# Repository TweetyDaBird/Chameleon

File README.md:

# The Fat Chameleon 

## Features
**Chameleon is a grid type orthogonal keyboard with two optional layouts in one single PCB.** Being able to break off the bottom row allows both a 5x12 layout similar to the popular Preonic and a 4x12 layout similar to the equally popular little brother Planck on the same PCB. 

Using the more common 19.05 mm grid spacing (vs Preonic & Planck's unique 19 mm) this PCB fit's several popular 'aftermarket' keyboard cases intended for JJ40/JJ50 and BM40 PCB's without modification. (Please read below!)

Being fully hot-swap and with PCB mounted stabilizers, Chameleon adds support for up to four encoders and a bottom row allowing either a single stabilized 2u key or two 2u keys in the middle, allowing for a layout that suits most users. If used as a 5 row keyboard, the bottom encoders can alternatively be placed at the edges on the second row, but **not more than one per corner.** 

The Chameleon features 8 bottomfacing RGB LEDs for underglow effects or to be used for layer indication or similar. 

**Please Note! This PCB does NOT fit a Planck/Preonic case! You will need a different case to complete the build!**

### Main Features:
* QMK and VIAL compatible, fully programmable keyboard**
* RP2040 MCU, Dual-core Arm Cortex M0+ processor, flexible clock running up to 133 MHz
* 264KB of SRAM, and 4MB of on-board Flash memory
* USB-C connector, (USB 1.1 device and host support)
* Low-power sleep and dormant modes
* Drag-and-drop programming using mass storage over USB
* Kaihl hot-swap sockets for Cherry MX compatible switches (3 & 5-pin)
* Cherry Style PCB mounted stabilizers
* Two main layouts:
	* 5x12 with 58 to 60 keys
	* 4x12 with 46 to 48 keys (Break off bottom row) 
* Configurable bottom row:
	* Full 1u grid
	* 1x centered, stabilized 2u key
	* 2x centered,  stabilized 2u keys

### Optional add-ons:
* Support for up to 4 rotary encoders **(one encoder per corner)**
* Optional RGB underglow (8x SK6812 mini-e)
* FR4 Front plate (FR4 material, same as PCB), with full layout options (Black / White). This is designed to fit most/all existing cases of a tray (or burger) mounting type, 3D printed or CNC. Se below for listed tested cases.

**These options requires additional components not included in this listing and sold separately.**

## Assembly
**Little or no tools at all needed!** The PCB can be delivered fully soldered and ready to use, either as a full matrix, or with your selection of rotary encoders (encoders need to be added to the order), or as a "DIY Kit" with the hotswap sockets for the 6 encoder positions not soldered.

The 8 optional RGB LED's needs to be soldered in place if used. (These are pre-soldered together with the encoders/hot-swap sockets at no extra cost, if that option is selected and all parts are purchased in the same order).

# Case & Plate
**The design is made to fit any existing cases for JJ40/JJ50 & BM40 both CNC and 3D printed.** This means that existing cases with an *integrated* plate is then limited to the layout options supported by that case/plate even if the PCB supports more layouts. 

#### Cases verified to work:

- [JJ50 Aluminium & Acrylic Case](https://kprepublic.com/collections/jj50-50/products/anodized-aluminium-case-for-jj50-50-custom-keyboard-acrylic-diffuser-rotary-brace-similar-with-preonic)
- [JJ50 Stainless Steel Case](https://kprepublic.com/collections/jj50-50/products/stainless-steel-bent-case-enclosed-case-for-jj50-jj50-50-custom-keyboard-acrylic-panels-acrylic-panel-diffuser-similar-preonic)
- [JJ40 Aluminium Tray Case](https://kprepublic.com/products/anodized-aluminium-jj40-bm40-flat-case-metal-feet-black-sliver-grey-for-40-mini?_pos=1&_sid=b33f69eef&_ss=r)
- [JJ40 Aluminium & Acrylic Case](https://kprepublic.com/products/anodized-aluminium-case-for-jj40-40-custom-keyboard-acrylic-panels-acrylic-diffuser-jj40-rotary-brace-supporter-for-planck?_pos=4&_sid=b33f69eef&_ss=r)
- [Poseidon PSD40 Case Anodized](https://kprepublic.com/products/poseidon-psd40-case-anodized-aluminium-case-for-custom-mechanical-keyboard-black-siver-grey-blue-red-for-jj40-bm40-bm40-rgb?_pos=5&_sid=b33f69eef&_ss=r) 
- [Poseidon PSD40 Case Electonplated](https://kprepublic.com/products/kp-poseidon-psd40-case-electrophoresis-cnc-case-for-custom-mechanical-keyboard-yellow-purple-cyan-white-for-jj40-bm40-bm40-rgb?_pos=6&_sid=b33f69eef&_ss=r)

*Mounting hardware is associated with the case, and not delivered with the Chameleon PCB and Plate.

## Front Plate
**A front plate in FR4 (PCB core material) is available as an add-on, but may not fit all cases.** To be as much a "one size fit's all" plate, this plate has rounded corners, which may leave gaps in the corners on some cases.

## 3D-print a case
**This is an adaptation of the Olkb Low Pro, ie low profile case for the Planck**, slightly re-designed to fit the 'normal' key spacing of the JJ40/JJ50 PCB and available as two designs to fit either the Planck or Preonic layout. Fully compatible with the FR4 front plate.
- [JJ50 - "Preonic" LoPro case](https://github.com/TweetyDaBird/Chameleon/blob/Development/JJ50_BM50_low_pro.zip)
- [JJ40 & BM40 - "Planck" LoPro case](https://github.com/TweetyDaBird/Chameleon/blob/Development/JJ40_BM40_low_pro.zip)

#### Examples of a 3D-printed case in white (Including the top image):

## Sandwich type case/plates
A full sandwich type case in FR4 material will be added at a later date for those interested, but is for now WIP.

# Making Chameleon yourself
**Chameleon is open source / open hardware, and can be manufactured by anyone. The release contains all the neccesary files like parts lists, positions files etc for a full PCB/SMT production.** 

The formatting and files are geared towards [JLCPCB](http://jlcpcb.com), but never tested as such, as I only manufacture the PCB then do the assembly myself (at least until this reaches a volume justifying full SMT production).

The components are small enough that you would have to be highly skilled to attempt to assemble this either as hand soldered, or small scale/DIY SMT. I would highly recommend ordering the PCB as fully assembled unless you know you have the neccesary skill-set.

## Buy a kit!
I sell complete kits, making it easy to build your keyboard, and it also supports prototypes for new wacky ones. 

## Discord for build help and discussions!

# License

[![CC BY-SA 4.0][cc-by-sa-shield]][cc-by-sa] - This work is licensed under a
[Creative Commons Attribution-ShareAlike 4.0 International License][cc-by-sa].

[cc-by-sa]: http://creativecommons.org/licenses/by-sa/4.0/
[cc-by-sa-shield]: https://img.shields.io/badge/License-CC%20BY--SA%204.0-lightgrey.svg

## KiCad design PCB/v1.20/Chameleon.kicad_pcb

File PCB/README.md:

# Chameleon PCB

## Change Log:
- v1.00 - Initial Release

- v1.01 - Second Release
  - Corrected RGB
  - Tweaked outline for easier removal of bottom row
  
- v1.11 - Third Release
  - Corrected USB Port position
  
- v1.20 - Third Release
  - Corrections to silkscreen.
<<<<<<< HEAD
  - Marking the spacer mounting holes for Planck/Preonic
=======
  - Marking the spacer mounting holes for Planck/Preonic
  - Marking Sockets for layout.
  - Added socket warning.
  - Add CE/RoHS marking.

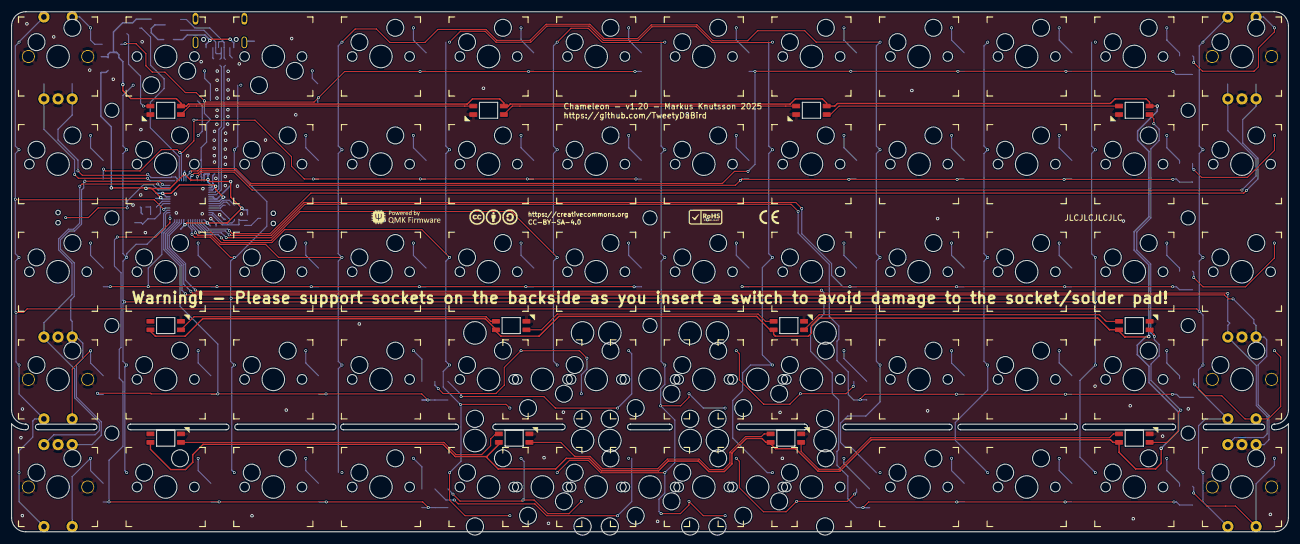
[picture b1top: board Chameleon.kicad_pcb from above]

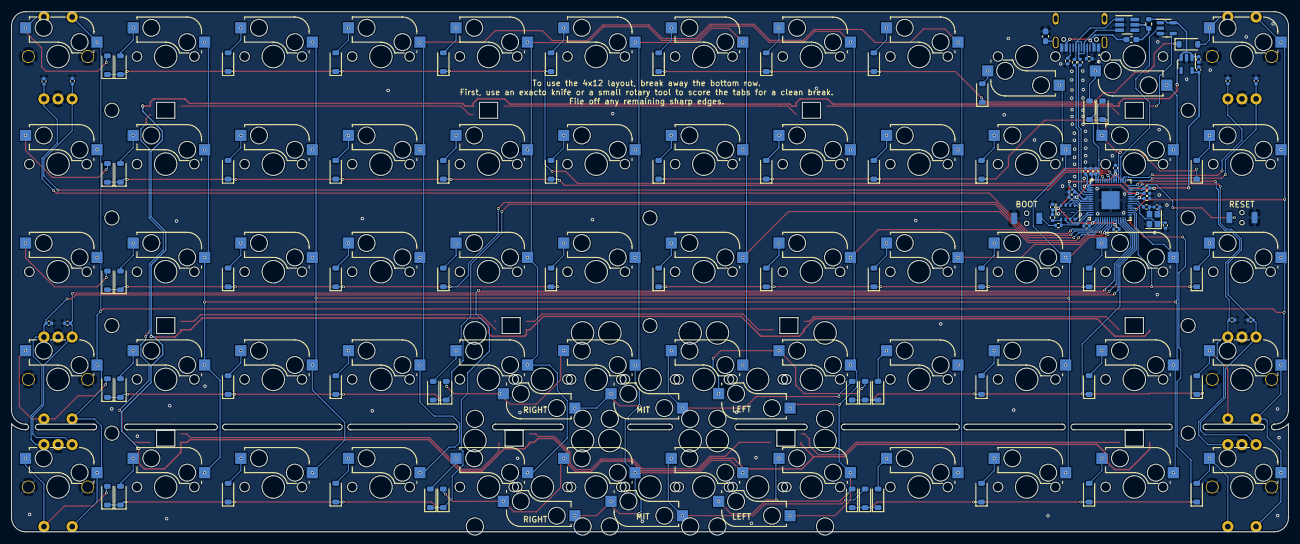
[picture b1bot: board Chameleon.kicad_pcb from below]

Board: 2 copper layers, 226.0 x 92.0 mm, 201 parts (115 on the bottom side), 120 nets.

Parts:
C1, C8, C11, C12: 1uF; C_0402_1005Metric
C2, C3, C4, C5, C6, C7, C9, C10, C13, C16, C17, C18, C19, C20, C21, C22, C23: 100nF; C_0402_1005Metric
C14, C15: 30pF; C_0402_1005Metric
D1, D2, D3, D4, D5, D6, D7, D8, D9, D10, D11, D12, D13, D14, D15, D16, D17, D18, D19, D20, D21, D22, D23, D24, D25, D26, D27, D28, D29, D30, D31, D32, D33, D34, D35, D36, D37, D38, D39, D40, D41, D42, D43, D44, D45, D46, D47, D48, D49, D50, D51, D52, D53, D54, D55, D56, D57, D58, D59, D60: 1N4148W; D_SOD-123
F1: 0603L050/6AR; R_0603_1608Metric
FB1, FB2: BLM18SG700TZ1D; C_0603_1608Metric_Pad1.08x0.95mm_HandSolder
H1, H2, H3, H4, H5, H6, H7, H8, H9, H10: Spacer_PCB; Spacer Plate hole
Logo1: CC-BY-SA-4.0; CC_BY_SA_40_line
Logo2: QMK_Logo; Powered_by_QMK
Logo3: CE
Logo4: RoHS; RoHs
R1, R2: 5.1K; R_0402_1005Metric
R3, R7: 10K; R_0402_1005Metric
R4, R10: 1K; R_0402_1005Metric
R5, R6: 27R; R_0402_1005Metric
RGB1, RGB2, RGB3, RGB4, RGB5, RGB6, RGB7, RGB8, RGB9, RGB10, RGB11, RGB12: SK6812MINI-E; RGB_SK6812MINI-E
ST1, ST2, ST3, ST4, ST5, ST6: Stabilizer_2u_MX; Stabilizer_Cherry_MX_2.00u
SW1, SW12: SW_MX_HotSwap_Encoder
SW2, SW3, SW4, SW5, SW6, SW7, SW8, SW9, SW10, SW11, SW13, SW14, SW15, SW16, SW17, SW18, SW19, SW20, SW21, SW22, SW23, SW24, SW25, SW26, SW27, SW28, SW29, SW30, SW31, SW32, SW33, SW34, SW35, SW36, SW38, SW39, SW40, SW41, SW42, SW43, SW44, SW45, SW46, SW47, SW50, SW51, SW52, SW53, SW54, SW55, SW56, SW57, SW58, SW59, SW61, SW62, SW63, SW64, SW65, SW66: PG151101S11; SW_MX_HotSwap
SW37, SW48, SW49, SW60: SW_MX_HotSwap_Encoder_inverted
TACT1, TACT2: YTSA010
U1: SPX3819M5-L-3-3/TR; SOT-23-5
U2: W25Q32JVUUIQ; USON-8_4x3mm_P0.8mm
U3: RP2040; QFN-56-1EP_7x7mm_P0.4mm_EP3.2x3.2mm
U4: SN74LV1T34DBV; SOT-23-5
U5: SRV05-4; SOT-23-6_Handsoldering
USB1: USB_C_Receptacle_USB2.0; HRO_TYPE-C-31-M-12
Y1: TXM12M0004252LBCEO00T; Crystal_SMD_2520-4Pin_2.5x2.0mm

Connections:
+1V1: C8.1, C9.1, C10.1, U3.23 (DVDD), U3.45 (VREG_VOUT), U3.50 (DVDD)
+3V3: C1.1, C2.1, C3.1, C4.1, C5.1, C6.1, C7.1, C12.1, C13.1, R3.1, R7.1, U1.5 (OUT), U2.8 (VCC), U3.1 (IOVDD), U3.10 (IOVDD), U3.22 (IOVDD), U3.33 (IOVDD), U3.42 (IOVDD), U3.43 (ADC_AVDD), U3.44 (VREG_IN), U3.48 (USB_VDD), U3.49 (IOVDD)
+5V: C11.1, F1.2, RGB1.1 (VDD), RGB2.1 (VDD), RGB3.1 (VDD), RGB4.1 (VDD), RGB5.1 (VDD), RGB6.1 (VDD), RGB7.1 (VDD), RGB8.1 (VDD), RGB9.1 (VDD), RGB10.1 (VDD), RGB11.1 (VDD), RGB12.1 (VDD), U1.1 (IN), U1.3 (EN), U4.5 (VCC)
/DN: R6.1, U3.46 (USB_DM)
/DP: R5.1, U3.47 (USB_DP)
Col_0: SW1.1, SW1.S1, SW12.1, SW12.S1, SW13.1, SW24.1, SW25.1, SW36.1, SW37.1, SW37.S1, SW48.1, SW48.S1, SW49.1, SW49.S1, SW60.1, SW60.S1, U3.18 (GPIO15)
Col_1: SW2.2, SW11.1, SW14.1, SW23.1, SW26.1, SW35.1, SW38.1, SW47.1, SW50.1, SW59.1, U3.17 (GPIO14)
Col_2: SW3.2, SW10.1, SW15.1, SW22.1, SW27.1, SW34.1, SW39.1, SW46.1, SW51.1, SW58.1, U3.8 (GPIO6)
Col_3: SW4.1, SW9.1, SW16.1, SW21.1, SW28.1, SW33.1, SW40.1, SW45.1, SW52.1, SW57.1, U3.7 (GPIO5)
Col_4: SW5.1, SW8.1, SW17.1, SW20.1, SW29.1, SW32.1, SW41.1, SW44.1, SW53.1, SW56.1, SW61.2, SW64.2, U3.6 (GPIO4)
Col_5: SW6.1, SW7.1, SW18.1, SW19.1, SW30.1, SW31.1, SW42.1, SW43.1, SW54.1, SW55.1, SW62.1, SW63.2, SW65.1, SW66.2, U3.5 (GPIO3)
D+: R5.2, U5.1 (IO1), USB1.A6 (D+), USB1.B6 (D+)
D-: R6.2, U5.3 (IO2), USB1.A7 (D-), USB1.B7 (D-)
ENC1_A: C16.1, SW1.A, U3.29 (GPIO18)
ENC1_B: C17.2, SW1.B, U3.30 (GPIO19)
ENC2_A: C18.1, SW12.A, U3.39 (GPIO27_ADC1)
ENC2_B: C19.2, SW12.B, U3.2 (GPIO0)
ENC3_A: C20.1, SW37.A, SW49.A, U3.28 (GPIO17)
ENC3_B: C21.2, SW37.B, SW49.B, U3.27 (GPIO16)
ENC4_A: C22.1, SW48.A, SW60.A, U3.13 (GPIO10)
ENC4_B: C23.2, SW48.B, SW60.B, U3.12 (GPIO9)
Earth_Protective: FB2.1, USB1.S1 (SHIELD)
GND: C1.2, C2.2, C3.2, C4.2, C5.2, C6.2, C7.2, C8.2, C9.2, C10.2, C11.2, C12.2, C13.2, C14.2, C15.2, C16.2, C17.1, C18.2, C19.1, C20.2, C21.1, C22.2, C23.1, FB2.2, R1.1, R2.2, RGB1.3 (GND), RGB2.3 (GND), RGB3.3 (GND), RGB4.3 (GND), RGB5.3 (GND), RGB6.3 (GND), RGB7.3 (GND), RGB8.3 (GND), RGB9.3 (GND), RGB10.3 (GND), RGB11.3 (GND), RGB12.3 (GND), SW1.C (GND), SW1.MP (GND), SW12.C (GND), SW12.MP (GND), SW37.C (GND), SW37.MP (GND), SW48.C (GND), SW48.MP (GND), SW49.C (GND), SW49.MP (GND), SW60.C (GND), SW60.MP (GND), TACT1.1, TACT2.1, U1.2 (GND), U2.4 (GND), U3.19 (TESTEN), U3.57 (GND), U4.3 (GND), U5.2 (VN), USB1.A1 (GND), USB1.A12 (GND), USB1.B1 (GND), USB1.B12 (GND), Y1.2, Y1.4
unnamed: C15.1, R10.2, Y1.3
unnamed: D1.2 (A), SW1.2, SW1.S2
unnamed: D2.2 (A), SW2.1
unnamed: D3.2 (A), SW3.1
unnamed: D4.2 (A), SW4.2
unnamed: D5.2 (A), SW5.2
unnamed: D6.2 (A), SW6.2
unnamed: D7.2 (A), SW7.2
unnamed: D8.2 (A), SW8.2
unnamed: D9.2 (A), SW9.2
unnamed: D10.2 (A), SW10.2
unnamed: D11.2 (A), SW11.2
unnamed: D12.2 (A), SW12.2, SW12.S2
unnamed: D13.2 (A), SW13.2
unnamed: D14.2 (A), SW14.2
unnamed: D15.2 (A), SW15.2
unnamed: D16.2 (A), SW16.2
unnamed: D17.2 (A), SW17.2
unnamed: D18.2 (A), SW18.2
unnamed: D19.2 (A), SW19.2
unnamed: D20.2 (A), SW20.2
unnamed: D21.2 (A), SW21.2
unnamed: D22.2 (A), SW22.2
unnamed: D23.2 (A), SW23.2
unnamed: D24.2 (A), SW24.2
unnamed: D25.2 (A), SW25.2
unnamed: D26.2 (A), SW26.2
unnamed: D27.2 (A), SW27.2
unnamed: D28.2 (A), SW28.2
unnamed: D29.2 (A), SW29.2
unnamed: D30.2 (A), SW30.2
unnamed: D31.2 (A), SW31.2
unnamed: D32.2 (A), SW32.2
unnamed: D33.2 (A), SW33.2
unnamed: D34.2 (A), SW34.2
unnamed: D35.2 (A), SW35.2
unnamed: D36.2 (A), SW36.2
unnamed: D37.2 (A), SW37.2, SW37.S2
unnamed: D38.2 (A), SW38.2
unnamed: D39.2 (A), SW39.2
unnamed: D40.2 (A), SW40.2
unnamed: D41.2 (A), SW41.2, SW64.1
unnamed: D42.2 (A), SW42.2, SW65.2
unnamed: D43.2 (A), SW43.2, SW66.1
unnamed: D44.2 (A), SW44.2
unnamed: D45.2 (A), SW45.2
unnamed: D46.2 (A), SW46.2
unnamed: D47.2 (A), SW47.2
unnamed: D48.2 (A), SW48.2, SW48.S2
unnamed: D49.2 (A), SW49.2, SW49.S2
unnamed: D50.2 (A), SW50.2
unnamed: D51.2 (A), SW51.2
unnamed: D52.2 (A), SW52.2
unnamed: D53.2 (A), SW53.2, SW61.1
unnamed: D54.2 (A), SW54.2, SW62.2
unnamed: D55.2 (A), SW55.2, SW63.1
unnamed: D56.2 (A), SW56.2
unnamed: D57.2 (A), SW57.2
unnamed: D58.2 (A), SW58.2
unnamed: D59.2 (A), SW59.2
unnamed: D60.2 (A), SW60.2, SW60.S2
unnamed: FB1.1, USB1.A4 (VBUS), USB1.A9 (VBUS), USB1.B4 (VBUS), USB1.B9 (VBUS)
unnamed: R4.2, TACT1.2
unnamed: RGB1.4 (DIN), U4.4 (Y)
unnamed: RGB1.2 (DOUT), RGB2.4 (DIN)
unnamed: RGB2.2 (DOUT), RGB3.4 (DIN)
unnamed: RGB3.2 (DOUT), RGB4.4 (DIN)
unnamed: RGB4.2 (DOUT), RGB5.4 (DIN), RGB9.4 (DIN)
unnamed: RGB5.2 (DOUT), RGB6.4 (DIN)
unnamed: RGB6.2 (DOUT), RGB7.4 (DIN)
unnamed: RGB7.2 (DOUT), RGB8.4 (DIN)
unnamed: RGB9.2 (DOUT), RGB10.4 (DIN)
unnamed: RGB10.2 (DOUT), RGB11.4 (DIN)
unnamed: RGB11.2 (DOUT), RGB12.4 (DIN)
unnamed: U2.6 (CLK), U3.52 (QSPI_SCLK)
unnamed: U2.5 (DI(IO0)), U3.53 (QSPI_SD0)
unnamed: U2.2 (DO(IO1)), U3.55 (QSPI_SD1)
unnamed: U2.3 (IO2), U3.54 (QSPI_SD2)
unnamed: U2.7 (IO3), U3.51 (QSPI_SD3)
unnamed: R4.1, R7.2, U2.1 (~CS), U3.56 (QSPI_SS)
unnamed: R3.2, TACT2.2, U3.26 (RUN)
unnamed: C14.1, U3.20 (XIN), Y1.1
unnamed: R10.1, U3.21 (XOUT)
unnamed: R1.2, USB1.A5 (CC1)
unnamed: R2.1, USB1.B5 (CC2)
RGB: U3.31 (GPIO20), U4.2 (A)
Row_0: D1.1 (K), D2.1 (K), D3.1 (K), D4.1 (K), D5.1 (K), D6.1 (K), U3.41 (GPIO29_ADC3)
Row_1: D7.1 (K), D8.1 (K), D9.1 (K), D10.1 (K), D11.1 (K), D12.1 (K), U3.34 (GPIO22)
Row_2: D13.1 (K), D14.1 (K), D15.1 (K), D16.1 (K), D17.1 (K), D18.1 (K), U3.32 (GPIO21)
Row_3: D19.1 (K), D20.1 (K), D21.1 (K), D22.1 (K), D23.1 (K), D24.1 (K), U3.36 (GPIO24)
Row_4: D25.1 (K), D26.1 (K), D27.1 (K), D28.1 (K), D29.1 (K), D30.1 (K), U3.16 (GPIO13)
Row_5: D31.1 (K), D32.1 (K), D33.1 (K), D34.1 (K), D35.1 (K), D36.1 (K), U3.3 (GPIO1)
Row_6: D37.1 (K), D38.1 (K), D39.1 (K), D40.1 (K), D41.1 (K), D42.1 (K), U3.14 (GPIO11)
Row_7: D43.1 (K), D44.1 (K), D45.1 (K), D46.1 (K), D47.1 (K), D48.1 (K), U3.4 (GPIO2)
Row_8: D49.1 (K), D50.1 (K), D51.1 (K), D52.1 (K), D53.1 (K), D54.1 (K), U3.15 (GPIO12)
Row_9: D55.1 (K), D56.1 (K), D57.1 (K), D58.1 (K), D59.1 (K), D60.1 (K), U3.11 (GPIO8)
VBUS: F1.1, FB1.2, U5.5 (VP)

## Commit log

2023-08-24 Initial design
2023-08-27 prototype
    Tweaked to (probably) prototype status
2023-09-22 Added versioning
2023-09-22 v1.01
    - Fix silkscreen errors
    - Fix reset/boot button footprint
    - Move rightmost column of diodes for easier PCB handling
2023-09-22 Houskeeping, fixed filenames
2024-01-04 v1.10
    initial
2024-01-04 Plate v1.01
    initial
2024-01-04 files in the wrong place
2024-01-04 Added plate readme
2024-01-04 add images
2024-01-04 Add readme/changelog to PCB folder
2024-01-04 v1.10
    added interactive bom
2024-02-09 v1.10 created BOM
2024-02-09 v1.10
    Minor correction silkscreen
2024-03-19 1.00 update
    Housekeeping
2024-05-03 v1.11
    minor silkscreen correction
2024-05-04 Added plate drawing
2024-05-27 Skinny Chameleon
    v1.00
2024-06-05 Skinny Chameleon v1.1
    Fixed mounting holes
2024-06-13 Add readme for Skinny Chameleon
2024-06-13 Update README.md
    Updated to reflect the Skinny Chameleon's specs.
2024-07-25 Update README.md
    Added downloadable 3D print cases.
2024-08-16 Skinny Chamelelon v1.10
    - Updated Planck Mounting holes
    - Updated centering on USB (was centered on 19.05 spacing?)
2024-08-19 Split Skinny Chameleon
    Files are moved to a different Git
2025-03-25 Chameleon v1.20
2025-11-29 re-ordered files
2025-11-29 Chameleon v1.20
    # Conflicts:
    # Chameleon/PCB/README.md
2025-11-29 Rename project to 'The Fat Chameleon'
2025-11-29 Moved Case/Plate Designs to a separate Git

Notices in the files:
PCB/v1.20/Chameleon.kicad_pcb:
Licensed under Creative Commons BY-SA 4.0 International
